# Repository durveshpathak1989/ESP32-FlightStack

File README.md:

# ESP32-FlightStack

ESP32-FlightStack is an open-source quadcopter flight-control stack for DIY drones, embedded-systems research, and low-cost UAV experimentation.

A custom quadcopter flight controller built around the **Adafruit HUZZAH32 / ESP32-WROOM-32E**, written in Arduino C++ on top of FreeRTOS. The project targets both stable flight and rigorous embedded-systems research: real-time scheduling, sensor fusion, Wi-Fi telemetry, onboard logging, runtime PID tuning, autonomous calibration, and over-the-air firmware updates, all on a $10 microcontroller.

**Firmware version:** v6.1.0<br>
**Control loop:** 400 Hz, `esp_timer`-driven, pinned to Core 1<br>
**AHRS default:** Attitude EKF (switchable at runtime to Mahony or Madgwick)

**Good GitHub topics:** `esp32`, `quadcopter`, `drone`, `uav`, `flight-controller`, `flight-control`, `embedded-c`, `esp-idf`, `arduino`, `freertos`, `pid-controller`, `imu`, `sensor-fusion`, `attitude-estimation`, `mpu9250`, `bmp280`, `madgwick-filter`, `motor-control`, `esc`

**Search keywords:** ESP32 drone library, ESP32 quadcopter flight controller, open-source drone stack, DIY quadcopter firmware, embedded drone control, IMU sensor fusion, PID stabilization, ESP32 UAV framework

---

## Open The Arduino Sketch

Open this file in Arduino IDE:

```text
RC_FlightController/RC_FlightController.ino
```

The folder name and the `.ino` file name match on purpose. Arduino expects that shape:

```text
RC_FlightController/
  RC_FlightController.ino
  src/
    Submodules/
      CalManager/
      IMU/
      Madgwick/
      MahonyAHRS/
      MotorControl/
      ...
```

Think of `RC_FlightController.ino` like the pilot, and `src/Submodules` like the toolbox beside the pilot. When Arduino builds the sketch, it automatically compiles the tools in `src/Submodules`, so you should not need to move the libraries by hand.

`Madgwick` and `MahonyAHRS` are also under `src/Submodules`, so Arduino compiles them automatically with the rest of the flight code. The shared AHRS types live in `src/Submodules/AHRS`.

After cloning with submodules, compile from the sketch folder:

```bash
git submodule update --init --recursive
arduino-cli compile --fqbn esp32:esp32:esp32 RC_FlightController
```

---

## Ground Station

| Dashboard | OTA upload | Offline OSM map |
|---|---|---|
|  |  |  |

---

## What This Project Does

Core loop:

```
Read IMU → notch-filter → AHRS/EKF → read RC → cascaded PID → motor mixer → ESC PWM
```

Surrounding infrastructure:

```
RC iBUS parsing           Autonomous sensor calibration
BMP280 barometer          GPS position + velocity
Wi-Fi AP + HTTP server    Browser-based ground station
Runtime PID / AHRS tuning Onboard high-speed CSV flight log
OTA firmware upload        Offline OSM map
Timing jitter measurement  Dynamic FFT notch tracking
CPU utilization monitor    ToF altitude sensor (optional)
```

Development philosophy:

```
1. Make the system safe.
2. Make the sensors trustworthy.
3. Make ACRO/rate mode stable.
4. Tune ANGLE/self-level mode.
5. Improve telemetry, logging, and test rigor.
```

---

## Capability Summary

| Area | Current capability |
|---|---|
| MCU | Adafruit HUZZAH32 Feather / ESP32-WROOM-32E |
| RTOS | Dual-core FreeRTOS, 7 tasks |
| IMU | MPU-9250 / MPU-6500 over SPI at 400 Hz |
| AHRS | Runtime-selectable: EKF (default), Mahony, Madgwick |
| Vibration filter | Static notch + dynamic FFT-tracked notch (45–170 Hz) |
| RC | FlySky FS-i6X + FS-iA6B iBUS, 200 Hz |
| Flight modes | ANGLE (self-level), ACRO (rate), DISARMED, FAILSAFE |
| Control | Cascaded angle+rate PID, yaw heading-hold |
| Motors | X-frame mixer, PWM ESCs via ESP32 LEDC |
| Barometer | BMP280 over I²C, 20 Hz, vertical speed estimate |
| GPS | u-blox NEO-6M / GY-GPS6MV2, NMEA UART, 50 Hz drain |
| Telemetry | ESP32 Wi-Fi AP + HTTP JSON endpoints |
| Ground station | Single-file HTML GCS, no build step |
| Runtime tuning | Full gain/filter payload via `/tune`, rejected while armed |
| Onboard logging | 100 Hz ring-buffer CSV log, 100 rows (1 s), streamed via HTTP |
| Timing log | Welford jitter stats + 800-sample ring buffer via `/timing` |
| OTA | Browser `.bin` upload via `/update`, safety-gated |
| Calibration | Autonomous gyro + 6-position accel + magnetometer + ESC via RC |
| Offline maps | Local `.osm` file loaded in browser, no internet required |
| CPU monitor | Per-core utilization estimate via idle hook |
| ToF | VL53L4CX optional altitude sensor (I²C shared with BMP280) |

---

## Hardware

| Subsystem | Part | Notes |
|---|---|---|
| Flight controller | Adafruit HUZZAH32 / ESP32-WROOM-32E | Main MCU, dual-core, Wi-Fi |
| IMU | MPU-9250 / MPU-6500 / GY-91 | Gyro + accel; onboard AK8963 mag if present |
| Barometer | BMP280 | Pressure, temperature, altitude |
| GPS | GY-GPS6MV2 / u-blox NEO-6M | Latitude, longitude, speed, satellites |
| RC transmitter | FlySky FS-i6X | 10-channel |
| RC receiver | FlySky FS-iA6B | iBUS serial protocol |
| ESCs | Standard PWM ESCs | 50 Hz PWM, 1000–2000 µs pulse |
| Motors | 2212-class, ~920 KV | Quadcopter propulsion |
| Battery | 3S LiPo (11.1 V nominal, 12.6 V full) | Main power, measured through GPIO34 divider |
| BEC | 5 V BEC | Powers controller and receiver |
| ToF (optional) | VL53L4CX | Altitude, shared I²C bus |

---

## Pin Map

| Function | GPIO | HUZZAH32 label | Direction | Notes |
|---|---:|---|---|---|
| SPI SCK | 5 | SCK | ESP32 → IMU | MPU-9250 clock |
| SPI MOSI | 18 | MO | ESP32 → IMU | MPU-9250 data in |
| SPI MISO | 19 | MI | IMU → ESP32 | MPU-9250 data out |
| MPU CS | 33 | 33 | ESP32 → IMU | Chip select |
| MPU INT | 27 | 27 | IMU → ESP32 | Wired but not driven by firmware |
| BMP280 SDA | 21 | SDA | Bidirectional | I²C data (shared with ToF) |
| BMP280 SCL | 22 | SCL | ESP32 → sensor | I²C clock (shared with ToF) |
| GPS RX | 13 | 13 | GPS TX → ESP32 | UART1 |
| GPS TX | 17 | 17 | ESP32 → GPS | UART1, optional |
| iBUS RX | 16 | 16 | Receiver → ESP32 | UART2 |
| iBUS TX | 4 | 4 | — | Spare, not connected |
| Motor FL | 25 | 25 | ESP32 → ESC | Front-left, CCW |
| Motor FR | 15 | 15 | ESP32 → ESC | Front-right, CW |
| Motor RL | 14 | 14 | ESP32 → ESC | Rear-left, CW |
| Motor RR | 32 | 32 | ESP32 → ESC | Rear-right, CCW |
| Battery ADC | 34 | 34 | Divider -> ESP32 | ADC1 input-only; 235k/35k divider, sampled every 500 ms |

Free GPIO: 23 (cleanest), 26 (ADC2/Wi-Fi caveat), 36/39 (input-only). GPIO34 is used by the battery ADC.

### Battery Voltage Monitor

GPIO34 reads the 3S pack through a high-value divider and updates telemetry every 500 ms. The firmware is configured for:

```
Battery + -> 235k -> ADC node -> 35k -> GND
ADC node -> GPIO34
Divider scale: 7.7143
```

A 12.2 V pack should measure about 1.58 V at GPIO34. Use a multimeter on the ADC node before plugging into the ESP32; the ADC pin must stay below 3.3 V. A 1k series resistor into GPIO34 and a 0.1 uF capacitor from GPIO34 to GND are recommended for noise filtering and input protection. If your real resistor values differ, update `BATTERY_RTOP_OHMS`, `BATTERY_RBOTTOM_OHMS`, or `BATTERY_ADC_CAL_SCALE` in `RC_FlightController.ino`.

---

## Wiring Guide

### MPU-9250 / GY-91

| IMU pin | ESP32 pin | Notes |
|---|---|---|
| VCC | 3.3 V | Use 3.3 V only |
| GND | GND | Common ground |
| SCL / SCLK | GPIO 5 | SPI clock |
| SDA / MOSI | GPIO 18 | SPI MOSI |
| AD0 / MISO | GPIO 19 | SPI MISO |
| NCS / CS | GPIO 33 | Chip select — pull-up to 3.3 V if unused |
| INT | GPIO 27 | Wired to GPIO 27; firmware does not use it |

Expected `WHO_AM_I`:

```
0x71  MPU-9250
0x70  MPU-6500 / MPU-9250 gyro-accel die
```

If the AK8963 magnetometer is absent or unresponsive, roll and pitch remain accurate. Yaw will drift without magnetic heading correction.

---

### BMP280

| BMP280 pin | ESP32 pin | Notes |
|---|---|---|
| VCC | 3.3 V | |
| GND | GND | |
| SDA / SDI | GPIO 21 | I²C data |
| SCL / SCK | GPIO 22 | I²C clock |
| CSB | 3.3 V | Pull high to force I²C mode |
| SDO | GND or 3.3 V | GND → address `0x76`, 3.3 V → `0x77` |

The firmware scans both addresses automatically. If nothing is found, verify CSB is pulled high and SDO is tied to a rail.

---

### GPS (GY-GPS6MV2 / NEO-6M)

| GPS pin | ESP32 pin | Notes |
|---|---|---|
| VCC | 3.3 V or module VIN | Many NEO-6M boards have an onboard regulator |
| GND | GND | |
| TXD | GPIO 13 | GPS → ESP32 (UART1 RX) |
| RXD | GPIO 17 | ESP32 → GPS (optional) |

```
UART:     UART1
Baud:     9600
Protocol: NMEA 0183
Parsed:   GPRMC, GPGGA
```

Cold fix outdoors: 30–90 seconds. Indoor fix is unreliable. A blinking blue LED on the module typically indicates a live fix.

---

### FlySky FS-iA6B iBUS

| Receiver pin | ESP32 pin | Notes |
|---|---|---|
| iBUS port | GPIO 16 | UART2 RX — use the dedicated iBUS/S.BUS port |
| VCC | 5 V from BEC | Receiver accepts 4.0–6.5 V |
| GND | GND | |

```
UART:         UART2
Baud:         115200
Frame length: 32 bytes
Frame period: ~7 ms
Rate:         ~142 Hz from receiver, polled at 200 Hz by firmware
```

Use the **iBUS port** on the receiver, not the individual CH1–CH6 servo outputs.

---

### ESC and Motor

| Motor | GPIO | Position | Spin | Notes |
|---|---:|---|---|---|
| FL | 25 | Front-left | CCW | 33 Ω series resistor recommended |
| FR | 15 | Front-right | CW | 33 Ω series resistor recommended |
| RL | 14 | Rear-left | CW | 33 Ω series resistor recommended |
| RR | 32 | Rear-right | CCW | 33 Ω series resistor recommended |

ESC ground and ESP32 ground must share a common reference. Without this, motor signals behave unpredictably.

---

## Motor Layout and Mixer

X-frame, viewed from above:

```
            Front

    FL  CCW          FR  CW
    GPIO 25          GPIO 15

         \           /
          \         /
           \       /
            ---X---
           /       \
          /         \
         /           \

    RL  CW           RR  CCW
    GPIO 14          GPIO 32

            Rear
```

Mixer equations:

```
FL = throttle + rollOut - pitchOut - yawOut
FR = throttle - rollOut - pitchOut + yawOut
RL = throttle + rollOut + pitchOut + yawOut
RR = throttle - rollOut + pitchOut - yawOut
```

Before first flight, verify signs by hand with props removed:

- Tilt right → correction must push right side up.
- Tilt left → correction must push left side up.
- Tilt nose down → correction must push nose up.
- Tilt nose up → correction must push nose down.
- Any reversal means a motor order, IMU axis sign, or mixer sign error. Fix it in code, not with PID tuning.

---

## RC Channel Mapping

| Channel | Transmitter control | Firmware function |
|---|---|---|
| CH1 | Right stick L/R | Roll |
| CH2 | Right stick U/D | Pitch |
| CH3 | Left stick U/D | Throttle |
| CH4 | Left stick L/R | Yaw |
| CH5 | VrA knob | Spare |
| CH6 | VrB knob | ESC calibration trigger (full-right = request) |
| CH7 | SWA | Arm / disarm |
| CH8 | SWB | ANGLE / ACRO mode |
| CH9 | SWC | Accelerometer calibration confirmation |
| CH10 | SWD | Calibration trigger (rising edge, disarmed only) |

---

## Flight Modes

### DISARMED

Motors are off. Permitted actions:

- Sensor calibration
- Runtime tuning via `/tune`
- OTA upload via `/update`
- Bench sensor checks
- Level-zero capture (SWB high while disarmed)

### ANGLE mode

Self-leveling. The stick commands a target lean angle. When the stick centres, the target returns to zero and the quad levels itself.

```
RC stick → target angle → angle PID → target rate → rate PID → motor mixer
```

Tune ACRO mode first. Then add ANGLE mode.

### ACRO mode

Rate mode. The stick commands angular velocity. Releasing the stick stops rotation but does not self-level.

```
RC stick → target rate → rate PID → motor mixer
```

### Yaw heading hold

When the yaw stick is within `yaw_deadband` of centre, the firmware holds the last commanded heading using a yaw angle PID. Moving the stick beyond the deadband switches to rate mode for yaw.

### FAILSAFE

If iBUS frames stop arriving, the receiver driver marks the signal invalid and motor outputs are cut immediately.

---

## FreeRTOS Task Architecture

| Task | Core | Priority | Stack (words) | Rate | Purpose |
|---|---:|---:|---:|---:|---|
| `taskControl` | 1 | 5 | 10240 | 400 Hz (esp_timer) | IMU, AHRS, PID, motor output |
| `taskRC` | 0 | 3 | 6144 | 200 Hz | iBUS parsing, arm/cal triggers |
| `taskGPS` | 0 | 1 | 4096 | 50 Hz | GPS NMEA drain and parse |
| `taskSerial` | 0 | 1 | 4096 | 20 Hz | Serial status and PID trace |
| `taskBMP` | 0 | 1 | 3072 | 20 Hz | BMP280 read, vertical speed |
| `taskCPU` | 0 | 1 | 3072 | 2 Hz | CPU utilization estimate |
| `taskWiFi` | 0 | 1 | 12288 | Event-driven | HTTP server, telemetry, OTA |

Core 1 is entirely dedicated to the control loop. All communication and slower sensors run on Core 0.

The control loop is released by an `esp_timer` ISR calling `xTaskNotifyGive()` every 2500 µs. `vTaskDelay()` is not used in `taskControl` because the FreeRTOS tick resolution on this build can be coarser than 2.5 ms.

---

## AHRS / Attitude Estimation

The firmware supports three attitude estimators, switchable at runtime via `/tune` without rebooting:

| Mode | `ahrs_filter_mode` | Description |
|---|---:|---|
| EKF (default) | 0 | 6-DOF or 9-DOF extended Kalman filter with gyro bias estimation |
| Mahony | 1 | Complementary filter, fast, low CPU cost |
| Madgwick | 2 | Gradient-descent complementary filter |

Switching estimator resets both EKF and Madgwick state to avoid attitude transients from stale quaternions.

**Pipeline order:** raw IMU → static notch filter → dynamic notch filter → AHRS → PID.

---

## Signal Filtering

### Static notch filter

A biquad notch filter is applied to all 6 IMU axes (3 accel + 3 gyro) before the AHRS. Default centre frequency: 90 Hz, Q: 8. Both are tunable at runtime.

### Dynamic FFT notch tracking

The `SpectrumAnalyzer` collects IMU data and runs an FFT. Every 250 ms (10 Hz), `updateDynamicNotchFromFFT()` finds the dominant gyro peak in the 45–170 Hz range and updates the notch centre frequency toward it using an exponential smoothing step capped at 2 Hz per update. The notch will not track while disarmed or below 15% throttle.

---

## Runtime Tuning

POST to `/tune` with a JSON body while **disarmed**. Any key can be omitted. The request is rejected while armed.

### Pilot limits

| Key | Default | Meaning |
|---|---:|---|
| `max_angle_deg` | 5.0 | Maximum lean in ANGLE mode (degrees) |
| `max_rate_dps` | 120.0 | Maximum roll rate in ACRO (deg/s) |
| `max_pitch_rate_dps` | 120.0 | Maximum pitch rate in ACRO (deg/s) |
| `yaw_max_rate_dps` | 20.0 | Maximum yaw rate (deg/s) |
| `yaw_deadband` | 0.02 | Stick fraction below which heading hold activates |

### PID authority limits

| Key | Default | Meaning |
|---|---:|---|
| `roll_output_limit` | 0.120 | Max roll correction before mixing |
| `pitch_output_limit` | 0.120 | Max pitch correction before mixing |
| `yaw_output_limit` | 0.120 | Max yaw correction before mixing |

### Throttle shaping

| Key | Default | Meaning |
|---|---:|---|
| `throttle_expo` | 0.70 | Softens low-throttle response |
| `throttle_up_rate_per_sec` | 0.50 | Max throttle increase rate per second |
| `throttle_down_rate_per_sec` | 0.50 | Max throttle decrease rate per second |
| `motor_idle` | 0.08 | Minimum motor output when armed and throttle above cut |
| `motor_max` | 1.00 | Maximum motor output cap |
| `throttle_cut` | 0.03 | Below this throttle, motors are cut |
| `idle_ramp_end` | 0.15 | Throttle fraction where idle blending ends |

### Rate PID (inner loop)

| Key | Default |
|---|---:|
| `pid_roll_kp` | 0.000900 |
| `pid_roll_ki` | 0.000001 |
| `pid_roll_kd` | 0.000000010 |
| `pid_pitch_kp` | 0.001900 |
| `pid_pitch_ki` | 0.000001 |
| `pid_pitch_kd` | 0.000000010 |
| `pid_yaw_kp` | 0.008000 |
| `pid_yaw_ki` | 0.00100 |
| `pid_yaw_kd` | 0.00000 |
| `pid_ilimit` | 50.0 |

### Angle PID (outer loop)

| Key | Default |
|---|---:|
| `pid_angle_roll_kp` | 1.50 |
| `pid_angle_roll_ki` | 0.00 |
| `pid_angle_roll_kd` | 0.000 |
| `pid_angle_pitch_kp` | 1.00 |
| `pid_angle_pitch_ki` | 0.00 |
| `pid_angle_pitch_kd` | 0.000 |
| `pid_angle_yaw_kp` | 1.00 |

### Notch filter

| Key | Default | Meaning |
|---|---:|---|
| `notch_enable` | true | Enable static notch |
| `notch_freq_hz` | 143.84 | Centre frequency (Hz) |
| `notch_q` | 10.0 | Q factor — higher = narrower |

### AHRS

| Key | Default | Meaning |
|---|---:|---|
| `ahrs_filter_mode` | 0.0 | 0 = EKF, 1 = Mahony, 2 = Madgwick |
| `mahony_kp` | (from object) | Mahony proportional gain |
| `mahony_ki` | (from object) | Mahony integral gain |
| `madgwick_beta` | 0.080 | Madgwick beta |

### Attitude EKF

| Key | Default | Meaning |
|---|---:|---|
| `ekf_angle_q` | 0.0008 | Process noise — angle states |
| `ekf_bias_q` | 0.000001 | Process noise — gyro bias states |
| `ekf_accel_r` | 0.400 | Accel measurement noise (higher = trust less) |
| `ekf_mag_r` | 0.200 | Magnetometer measurement noise |
| `ekf_mag_declination_deg` | 0.0 | Local magnetic declination |
| `ekf_mag_yaw_offset_deg` | 0.0 | Yaw alignment offset |
| `ekf_mag_yaw_sign` | 1.0 | +1 or -1 to correct mag axis sign |

---

## Serial Commands

| Command | Effect |
|---|---|
| `p` | Toggle ~4 Hz `[PID]` tuning trace on/off (off at boot) |

---

## HTTP Endpoints

The ESP32 creates a Wi-Fi access point:

```
SSID:     ESP32-DRONE
Password: 12345678
IP:       192.168.4.1
```

| Endpoint | Method | Purpose |
|---|---|---|
| `/telemetry` | GET | Full flight state JSON |
| `/tune` | POST | Apply PID / AHRS / filter gains (disarmed only) |
| `/log?since=N` | GET | Calibration and system log lines since index N |
| `/timing` | GET | Jitter stats JSON (Welford mean, std, max, violations) |
| `/timing/reset` | POST | Reset jitter accumulator |
| `/timing/csv` | GET | Raw 800-sample period ring buffer as CSV |
| `/flightlog/csv` | GET | Freeze and download 100-row onboard flight log CSV |
| `/flightlog/reset` | POST | Clear onboard log and resume writing |
| `/update` | GET | OTA upload page |
| `/update` | POST | OTA firmware upload (disarmed, throttle low, motors off) |

Battery telemetry fields from `/telemetry`: `batteryVoltageV`, `batteryAdcV`, `batteryCellV`, `batteryPercent`, `batteryValid`, `batteryLow`, and `batteryCritical`.

---

## Onboard Flight Log

The firmware maintains a 100-row ring buffer sampled at 100 Hz (every 4th control cycle). Each row is approximately 320 bytes and captures:

```
Timestamps and loop count       RC stick inputs (all 10 channels)
IMU timing phases               Throttle (raw, shaped, smoothed)
Period and jitter               AHRS attitude (roll, pitch, yaw)
Raw and filtered IMU data       Control attitude (after level-zero offset)
Magnetometer                    PID targets, errors, and outputs
EKF gyro bias estimates         Motor commands and estimated RPM
Notch filter state              BMP280 altitude and vertical speed
AHRS mode and mag-accept flag   CPU utilization (Core 0 and Core 1)
```

Workflow:

```
POST /flightlog/reset  → clears buffer and re-enables writing
ARM + fly
DISARM
GET  /flightlog/csv    → freezes buffer and streams CSV
```

To extend the log beyond 1 second, increase `FLIGHT_LOG_SIZE` (currently 100). At 320 bytes per row and ~300 KB free heap in a typical flight build, 300 rows (~3 seconds) is a safe upper bound.

---

## Autonomous Calibration

Calibration runs inside `taskControl` on Core 1 and is triggered by RC or HTTP. While calibration is active, the flight loop is blocked and motor outputs are inhibited.

### IMU calibration (guided, via SWD + SWC)

1. **Disarm** the craft (SWA low).
2. Flip **SWD** up to request calibration.
3. **Gyro phase** (automatic): place the drone flat and still. The firmware waits 3 seconds for settling, then samples 5 seconds of gyro data.
4. **Accel phase** (6 positions): flip **SWC** up to confirm each orientation. The firmware prompts each pose over the serial log.
5. **Magnetometer phase** (if present): rotate the drone slowly in all axes for 30 seconds.
6. Calibration saves to NVS (non-volatile storage) and loads automatically on every subsequent boot.

### ESC calibration (via VrB + SWC)

1. **Disarm** and set throttle to minimum.
2. Raise **VrB** (CH6) to full right.
3. Confirm with **SWC** when prompted.
4. Lower VrB to cancel at any time.

Calibration is rejected if the craft is armed or throttle is above `throttle_cut`.

---

## Software Level-Zero Trim

While **disarmed** with **SWB** held high (ACRO position), the firmware averages 1.2 seconds of AHRS attitude output and saves it as a roll/pitch/yaw offset. All subsequent control attitude values are computed relative to this zero. This corrects for frame twist or a non-level mounting surface without touching IMU calibration or the AHRS quaternion.

---

## Wi-Fi Ground Station

The browser-based GCS (`Simulation/DroneGCS.html`) connects directly to `http://192.168.4.1`. No build step or internet connection is required once the file is open.

Features:

- Live attitude display (roll, pitch, yaw)
- Motor output gauges
- Battery voltage, percentage, and low/critical visual
- PID output traces
- Barometer altitude and vertical speed
- GPS position and satellite count
- Timing jitter chart
- Full PID, AHRS, and filter tuning panel
- Calibration log stream
- OTA firmware upload panel

---

## Offline OSM Map

When connected to `ESP32-DRONE`, the laptop has no internet. Tile-based maps will not load. The offline OSM workflow serves a local map extract from the laptop instead.

Recommended folder layout:

```
DroneGCS/
├── DroneGCS.html
└── YourArea.osm
```

Run a local server:

```bash
cd path/to/DroneGCS
python3 -m http.server 8080
```

Open in the browser:

```
http://localhost:8080/DroneGCS.html
```

The GCS fetches telemetry from `http://192.168.4.1` while the OSM file is loaded locally. Use only a small OSM extract around your test field — large files slow the browser significantly.

Good sources for OSM extracts:

- OpenStreetMap.org export (small bounding box)
- BBBike extract service
- Geofabrik extract, cropped with Osmium or QGIS

The map is for situational awareness only — it is not autonomous navigation.

---

## OTA Firmware Update

### Arduino IDE partition scheme

Select before the first USB flash:

```
Tools → Partition Scheme → Minimal SPIFFS (1.9MB APP with OTA and 190KB SPIFFS)
```

This provides two app slots for OTA while giving the application maximum flash space. The GCS is served from the laptop, so a large SPIFFS partition is not needed.

Do **not** use `No OTA` or `Huge APP without OTA`.

### Exporting the binary

1. Select the correct board and partition scheme.
2. Flash once by USB.
3. Click **Sketch → Export Compiled Binary**.
4. Click **Sketch → Show Sketch Folder** and find the build output.
5. Upload the correct file through OTA:

```
RC_FlightController.ino.bin          ← upload this
```

Do not upload:

```
boot_app0.bin
RC_FlightController.ino.bootloader.bin
RC_FlightController.ino.partitions.bin
RC_FlightController.ino.merged.bin
RC_FlightController.ino.elf
```

### OTA safety gate

The firmware permits OTA only when all three conditions hold:

```
armed == false
throttle <= throttle_cut
all motor outputs <= 0.001
```

Remove propellers before every OTA session.

---

## First-Time Setup

### Step 1 — Bench safety

```
REMOVE PROPELLERS
```

### Step 2 — Flash firmware

```
Board:          Adafruit ESP32 Feather
Upload speed:   921600
Partition:      Minimal SPIFFS (1.9MB APP with OTA)
```

### Step 3 — Read the boot log

Open Serial Monitor at **115200 baud**. Expected output:

```
[BOOT] IMU... OK
[BOOT] AK8963 magnetometer: DETECTED  (or NOT FOUND)
[BOOT] BMP280... OK  (or not found)
[BOOT] GPS (GY-GPS6MV2)...
[BOOT] NVS calibration... loaded  (or none)
[BOOT] iBUS ready.
[BOOT] All tasks running.
[BOOT] Ground station: http://192.168.4.1
[BOOT] Free heap: XXXXXX bytes
```

If the IMU fails, halt is immediate — check SPI wiring and 3.3 V power.

### Step 4 — Check RC

Turn on the transmitter and confirm:

```
[iBUS] ~142 Hz good | 0 bad/s | 0 bad total   (should appear every second)
```

Confirm sticks, SWA arm/disarm, SWB mode change, SWD calibration trigger.

### Step 5 — Calibrate sensors

With props removed:

1. Keep SWA disarmed.
2. Flip SWD up (rising edge triggers calibration).
3. Follow prompts in the serial log.
4. Calibration saves to NVS and reloads on every boot.

### Step 6 — Verify motor order and mixer

With props still removed:

- Arm the craft.
- Raise throttle slightly.
- Confirm FL/FR/RL/RR match physical position.
- Tilt the frame by hand and confirm PID corrections oppose the tilt.
- Disarm before anything else.

### Step 7 — First powered hover

```
Small props
max_angle_deg = 10
motor_max = 0.60
angle I gains = 0
Conservative throttle
Short hover bursts
```

Do not attempt to hover until Step 6 is confirmed.

---

## Tuning Order

1. Props off: verify sensor sign and motor correction direction (Step 6).
2. ACRO mode first: tune `pid_roll_kp`, `pid_pitch_kp` for stable rate response with no oscillation.
3. Add `kd` carefully — unfiltered derivative amplifies gyro noise at 400 Hz.
4. ANGLE mode second: tune `pid_angle_roll_kp`, `pid_angle_pitch_kp`.
5. Keep angle I gains at zero until P and D are settled.
6. Tune yaw separately — yaw authority is intentionally limited to `yaw_output_limit = 0.2`.
7. Use `/flightlog/csv` and the timing monitor to verify loop timing stays within budget during tuning.

---

## Timing Diagnostics

`GET /timing` returns a JSON object with:

```json
{
  "count": 12000,
  "target_us": 2500,
  "period_mean_us": 2501.3,
  "period_std_us": 18.4,
  "jitter_max_us": 142,
  "jitter_mean_us": 12.1,
  "jitter_violations": 3,
  "violation_thresh_us": 100,
  "p50_us": 2500,
  "p95_us": 2528,
  "p99_us": 2571
}
```

`GET /timing/csv` streams the last 800 raw period samples for offline analysis.

`POST /timing/reset` clears all accumulators for a clean measurement window.

The `[TIME]` serial line prints once per second:

```
[TIME] period=2501us jitter=+1us ctrl=XXXus full=XXXus headroom=+XXXus ...
```

A negative `headroom` value means a control overrun — the current cycle took longer than the 2500 µs budget.

---

## Troubleshooting

### Serial garbage

Baud rate must be **115200**. Confirm in the IDE Serial Monitor and any terminal emulator.

### IMU not found

```
3.3 V power to MPU
SPI wiring: SCK=5, MOSI=18, MISO=19, CS=33
No other SPI device sharing the bus without its own CS
```

### BMP280 not found

```
SDA=21, SCL=22
CSB pulled high to 3.3 V
SDO set for expected I²C address (0x76 or 0x77)
3.3 V power
```

### GPS no fix

```
Move outdoors with clear sky
Wait 30–90 seconds for cold fix
GPS TXD → GPIO 13
Antenna facing up
```

### No RC input / failsafe

```
iBUS port on receiver, not servo pins
GPIO 16 connected to iBUS signal wire
Receiver powered from 5 V BEC
Transmitter bound and powered
```

### Drone tips on throttle

Diagnose in this order:

1. Motor order (FL/FR/RL/RR positions).
2. Prop direction (CW/CCW per motor position).
3. ESC signal wiring.
4. IMU axis signs.
5. Mixer signs.
6. Centre of gravity.
7. Frame twist.
8. PID gains (only after all above are confirmed correct).

**Never use PID tuning to compensate for a motor order or sign error.**

### GPS map blank

When connected to `ESP32-DRONE`, the laptop has no internet. Use the offline OSM workflow, or connect both devices to a shared hotspot.

### OTA rejected

OTA is gated on disarmed + throttle low + motors off. Confirm all three in the GCS or serial log before uploading.

---

## Known Firmware Issues (v6.1.0)

The following issues are identified and tracked for the next release:

| # | Issue | Impact |
|---|---|---|
| 1 | `[MOTOR_SAT]` Serial.printf fires unconditionally at 400 Hz | Guaranteed control overrun while armed |
| 2 | Motor writes throttled to 200 Hz (`MOTOR_UPDATE_PERIOD_US = 5000`) | Up to 5 ms stale motor command per cycle |
| 3 | `[DYN_NOTCH_HOOK]` and `[DYN_FFT_INPUT]` debug prints inside the 400 Hz IMU block | ~7 ms Serial cost on the cycle they fire |
| 4 | `thrSmooth` static local not reset on disarm | Inherited throttle state after disarm/re-arm |
| 5 | AHRS mode falls back to EKF (mode 0) on mutex miss | One-cycle estimator switch during flight |
| 6 | `calLog()` called from Core 1 inside `applyTuningToObjects()` | Priority inversion risk against Wi-Fi task |
| 7 | Unfiltered derivative term in PID | Gyro noise amplification at high Kd |
| 8 | Single `pid_ilimit = 50` shared across rate (dps) and angle (deg) loops | Dimensionally inconsistent wind-up limit |
| 9 | `FLIGHT_LOG_SIZE = 100` but comment says 300 | Log is 1 s, not 3 s |
| 10 | GPIO34 battery divider calibration needs a real-hardware multimeter check | Incorrect divider ratio skews percentage and RPM estimate |

---

## Safety Rules

- **Remove propellers** before USB flashing, OTA, calibration, or bench tests.
- Never arm on USB power alone.
- Never attempt OTA while armed.
- Never tune while armed (the firmware enforces this for `/tune`).
- Keep first hover tests short and low.
- Use smaller props during early PID tuning.
- Keep a USB recovery path available at all times.
- GPS and map display are telemetry only — not navigation authority.

---

## Project Direction

This project supports both flight testing and embedded-systems research:

- ESP32 dual-core task partitioning and priority assignment
- `esp_timer` vs `vTaskDelay` for hard real-time control loops
- Wi-Fi interference with control-loop timing (characterised via `/timing`)
- Runtime filter tuning and AHRS mode switching without reboot
- OTA update safety gating
- Autonomous calibration usability over RC
- Offline field-map workflow
- Low-cost AHRS comparison (EKF vs Mahony vs Madgwick)
- Onboard high-speed logging for post-flight analysis
- LSTM-based fault prognosis using logged CSV data (companion research project)

The goal is a flying quadcopter that is also a rigorous test platform for every subsystem interaction.

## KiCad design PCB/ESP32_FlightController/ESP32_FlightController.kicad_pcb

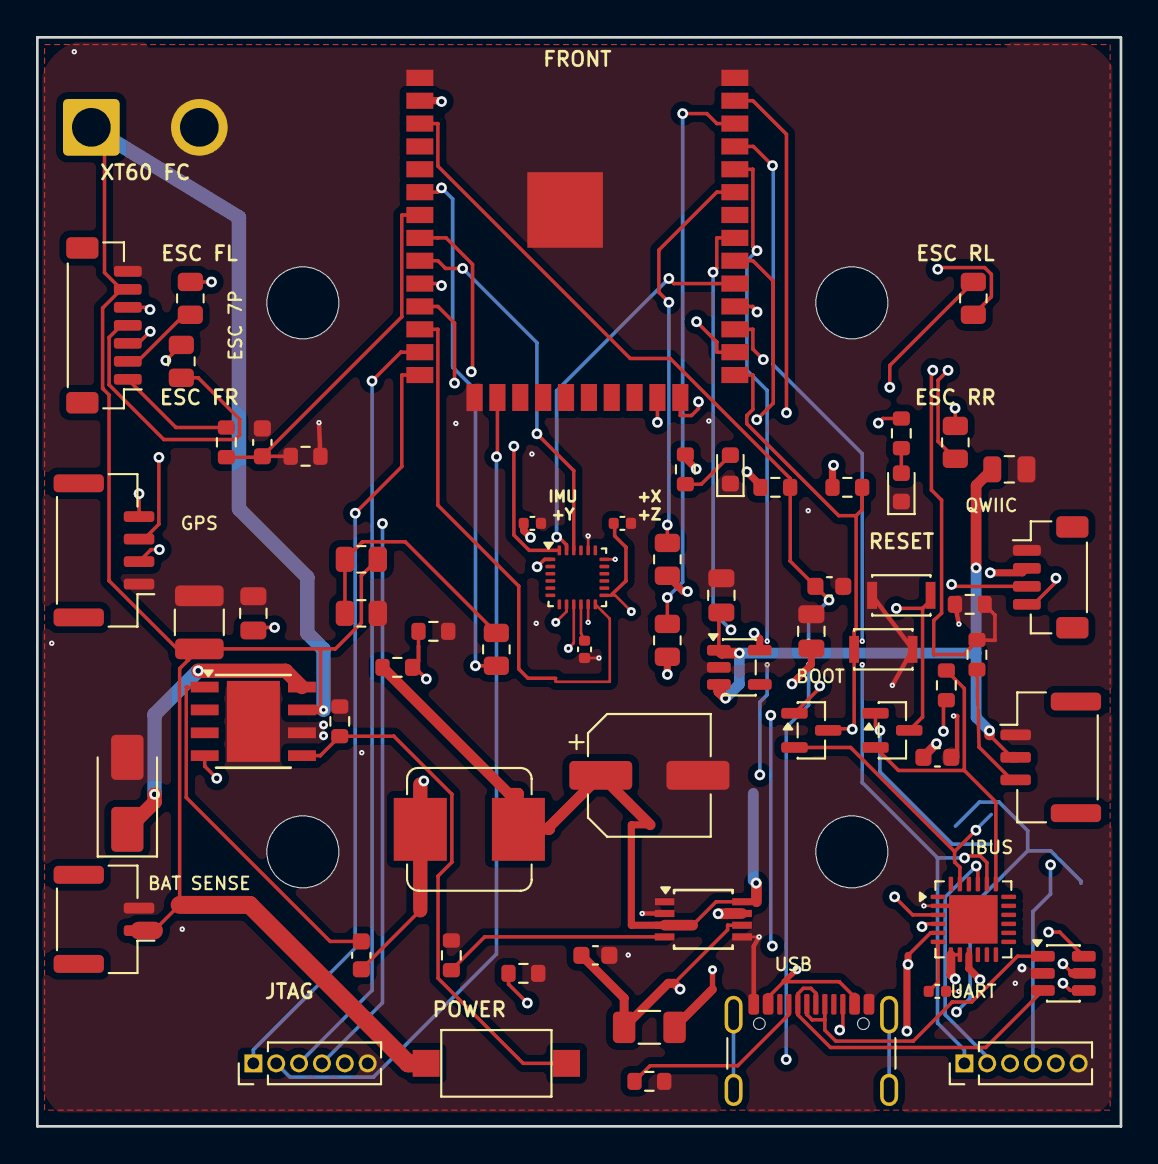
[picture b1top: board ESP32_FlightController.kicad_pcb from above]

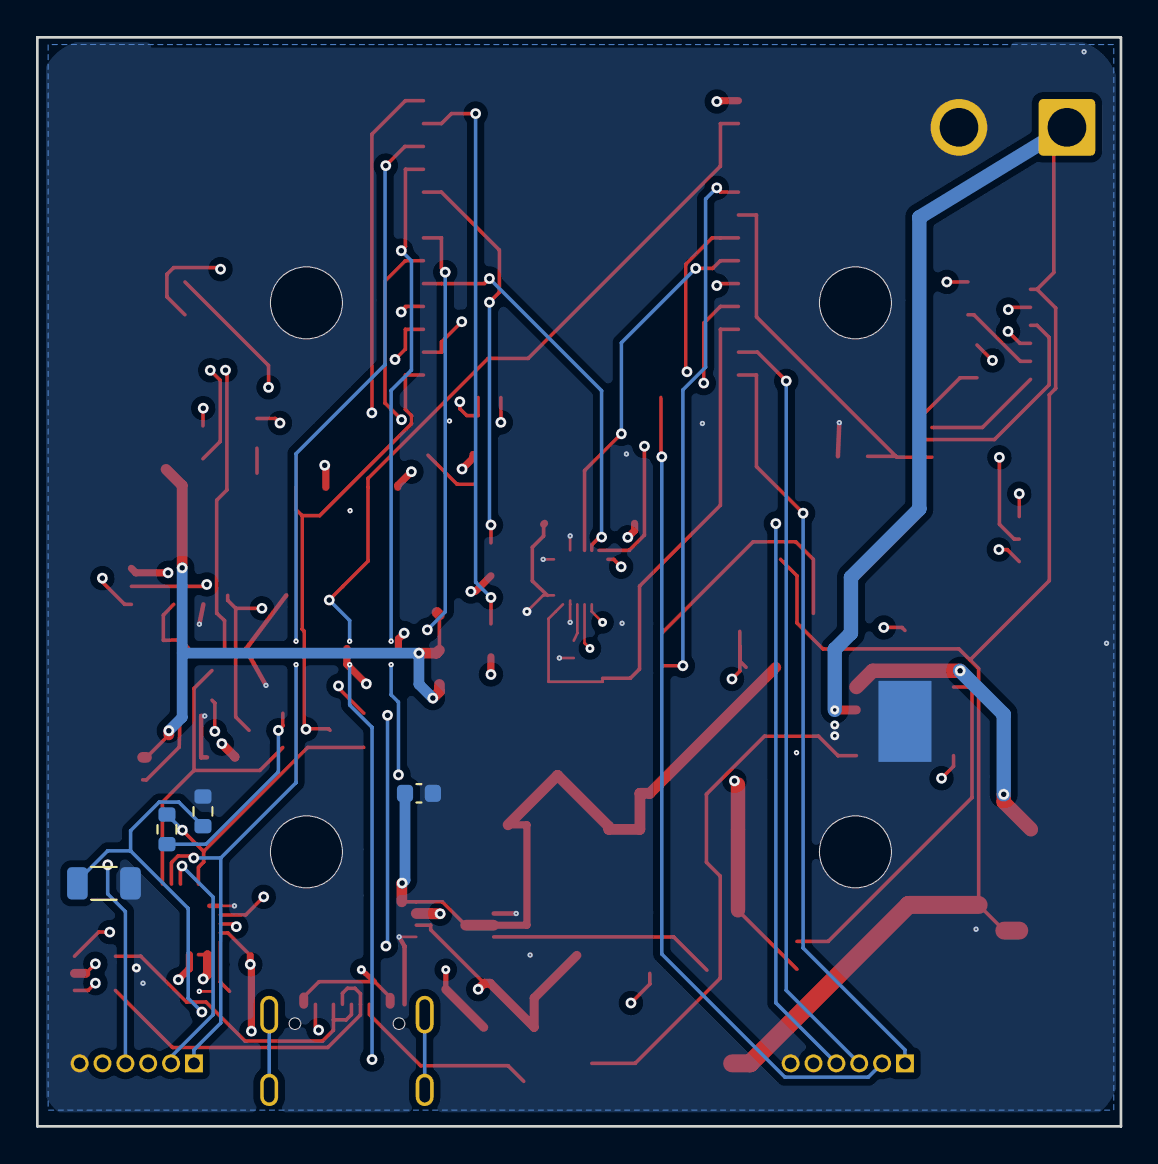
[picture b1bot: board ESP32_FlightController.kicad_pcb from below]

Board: 4 copper layers, 60.2 x 60.5 mm, 73 parts (4 on the bottom side), 59 nets.

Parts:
C1: 10uF/25V X7R; C_1210_3225Metric
C2: 100n; C_0805_2012Metric
C3: 10n; C_0603_1608Metric
C4: 220uF/10V LOW-ESR; CP_Elec_6.3x5.8
C5, C6: 10u; C_0805_2012Metric
C7: 1u; C_0603_1608Metric
C10: 10n X7R; C_0402_1005Metric
C11, C12, C13: 100n X7R; C_0402_1005Metric
C14: 4.7u X7R; C_0603_1608Metric
C15, C16, C19: 100n; C_0603_1608Metric
C17: 10u X7R; C_0805_2012Metric
C18: 1nF/2kV; C_1206_3216Metric
D1: B340A; D_SMA
D3: GREEN_POWER; LED_0603_1608Metric
D4: BLUE_STATUS; LED_0603_1608Metric
F1: 0.75A USB PTC; Fuse_1206_3216Metric
H1, H2, H3, H4: M4 / 30.5mm STACK; MountingHole_4mm
J1: XT60_FC_FEED_PIGTAIL; SolderWire-1.5sqmm_1x02_P6mm_D1.7mm_OD3mm
J2: 3S_BAT_SENSE; JST_GH_BM02B-GHS-TBT_1x02-1MP_P1.25mm_Vertical
J4: I2C_SENSOR_BUS; JST_SH_BM04B-SRSS-TB_1x04-1MP_P1.00mm_Vertical
J5: GPS_NEO6M; JST_GH_BM04B-GHS-TBT_1x04-1MP_P1.25mm_Vertical
J6: FLYSKY_IBUS; JST_GH_BM03B-GHS-TBT_1x03-1MP_P1.25mm_Vertical
J7: UART_PROGRAM; PinHeader_1x06_P1.27mm_Vertical
J8: JTAG_DEBUG; PinHeader_1x06_P1.27mm_Vertical
J9: USB_C_PROGRAM; USB_C_Receptacle_GCT_USB4105-xx-A_16P_TopMnt_Horizontal
J14: BLS60A_ESC_7PIN; JST_SH_BM07B-SRSS-TB_1x07-1MP_P1.00mm_Vertical
L1: 15uH SRP7028A-150M; L_Bourns_SRP7028A_7.3x6.6mm
Q1, Q2: MMBT3904; SOT-23
R1: 235k 1%; R_0805_2012Metric
R2: 35k 1%; R_0805_2012Metric
R3: 1k; R_0805_2012Metric
R4, R5: 4.7k; R_0805_2012Metric
R6, R21, R25: 10k 1%; R_0603_1608Metric
R7: 3.24k 1%; R_0603_1608Metric
R8, R9, R18, R19: 10k; R_0603_1608Metric
R10, R11, R12, R13: 220; R_0805_2012Metric
R14: 100k; R_0603_1608Metric
R15, R16: 5.1k; R_0603_1608Metric
R17: 499R (1A LIMIT); R_0603_1608Metric
R20: 1M; R_0603_1608Metric
R22, R23: 2.2k; R_0603_1608Metric
R24, R26: 20k 1%; R_0603_1608Metric
SW1: RESET; SW_SPST_CK_KXT3
SW2: CONTROLLER_POWER; SW_SPST_CK_RS282G05A3
SW3: BOOT; SW_SPST_CK_KXT3
U1: ESP32-WROOM-32E; ESP32-WROOM-32_Custom
U2: MPU-9250; InvenSense_QFN-24_3x3mm_P0.4mm
U3: TPS5430DDA; TI_SO-PowerPAD-8_NoUnderDrills
U4: AP2112K-3.3; SOT-23-5
U5: USBLC6-2SC6; SOT-23-6
U6: CP2102N-A02-GQFN24; QFN-24-1EP_4x4mm_P0.5mm_EP2.7x2.7mm
U7: TPS2113APW; TSSOP-8_3x3mm_P0.65mm

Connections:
+3V3: C6.1, C10.1, C11.1, J4.2, J5.2, J7.5, J8.5, R4.1, R5.1, R8.1, R9.1, R22.2, U1.2 (VDD), U2.1 (RESV_VDDIO), U2.8 (VDDIO), U2.13 (VDD), U4.5 (VOUT), U6.5 (VIO), U6.9 (~RST)
+5V: C5.1, C17.1, J6.2, U4.1 (VIN), U4.3 (EN), U7.7 (OUT)
/+5V_BUCK: C4.1, C15.1, L1.2, R6.1, U7.3 (VSNS), U7.8 (IN1)
/AUTO_DTR: Q2.2 (E), R18.2, U6.23 (~DTR)
/AUTO_RTS: Q1.2 (E), R19.2, U6.19 (~RTS)
/BAT_ADC: C2.1, R3.1, U1.6 (IO34)
/BOOT_IO0: J7.4, Q2.3 (C), R9.2, SW3.1, U1.25 (IO0)
/BOOT_STATUS_LED: R23.2, U1.24 (IO2)
/BUCK_EN: R14.1, SW2.2 (B), U3.5 (EN)
/CP2102_VDD: C13.1, U6.6 (VDD)
/ESC_CURRENT_ADC: C19.1, R21.1, R24.1, U1.7 (IO35)
/ESC_CUR_RAW: J14.1, R21.2
/ESP_EN: C7.1, J7.3, Q1.3 (C), R8.2, SW1.2, U1.3 (EN)
/GPS_RX: J5.4, U1.37 (IO23)
/GPS_TX: J5.3, U1.28 (IO17)
/I2C_SCL: J4.3, R5.2, U1.36 (IO22)
/I2C_SDA: J4.4, R4.2, U1.33 (IO21)
/IBUS_RAW: J6.3, R25.2
/IBUS_RX: R25.1, R26.1, U1.27 (IO16)
/IMU_CS: U1.9 (IO33), U2.22 (~CS)
/IMU_INT: U1.12 (IO27), U2.12 (INT)
/JTAG_TCK: J8.2, U1.16 (IO13)
/JTAG_TDI: J8.1, U1.14 (IO12)
/JTAG_TDO: J8.4, U1.23 (IO15)
/JTAG_TMS: J8.3, U1.13 (IO14)
/MOTOR_FL: J14.2, R10.1
/MOTOR_FL_RAW: R10.2, U1.10 (IO25)
/MOTOR_FR: J14.4, R11.1
/MOTOR_FR_RAW: R11.2, U1.26 (IO4)
/MOTOR_RL: J14.3, R12.1
/MOTOR_RL_RAW: R12.2, U1.11 (IO26)
/MOTOR_RR: J14.5, R13.1
/MOTOR_RR_RAW: R13.2, U1.8 (IO32)
/SPI_MISO: U1.31 (IO19), U2.9 (AD0/MISO)
/SPI_MOSI: U1.30 (IO18), U2.24 (SDA/MOSI)
/SPI_SCK: U1.29 (IO5), U2.23 (SCL/SCLK)
/SW_NODE: C3.1, D1.1 (K), L1.1, U3.8 (PH)
/UART0_RX: J7.2, U1.34 (RXD0/IO3), U6.21 (TXD)
/UART0_TX: J7.1, U1.35 (TXD0/IO1), U6.20 (RXD)
/USB_CC1: J9.A5 (CC1), R15.1
/USB_CC2: J9.B5 (CC2), R16.1
/USB_CONN_DM: J9.A7 (D-), J9.B7 (D-), U5.3 (I/O2)
/USB_CONN_DP: J9.A6 (D+), J9.B6 (D+), U5.1 (I/O1)
/USB_DM: U5.4 (I/O2), U6.4 (D-)
/USB_DP: U5.6 (I/O1), U6.3 (D+)
/USB_SHIELD: C18.1, J9.SH (SHIELD), R20.1
/USB_VBUS: C14.1, C16.1, F1.1, U5.5 (VBUS), U6.7 (VREGIN), U6.8 (VBUS), U7.6 (IN2)
/USB_VBUS_RAW: F1.2, J9.A4 (VBUS), J9.A9 (VBUS), J9.B4 (VBUS), J9.B9 (VBUS)
/VBAT_RAW: C1.1, J1.1, J2.1, J14.6, R1.2, SW2.1 (A), U3.7 (VIN)
GND: C1.2, C2.2, C4.2, C5.2, C6.2, C7.2, C10.2, C11.2, C12.2, C13.2, C14.2, C15.2, C16.2, C17.2, C18.2, C19.2, D1.2 (A), D3.1 (K), D4.1 (K), J1.2, J2.2, J4.1, J5.1, J6.1, J7.6, J8.6, J9.A1 (GND), J9.A12 (GND), J9.B1 (GND), J9.B12 (GND), J14.7, R2.2, R7.2, R14.2, R15.2, R16.2, R17.2, R20.2, R24.2, R26.2, SW1.1, SW3.2, U1.1 (GND), U1.15 (GND), U1.38 (GND), U1.39 (GND), U2.11 (FSYNC), U2.18 (GND), U2.20 (RESV_GND), U3.6 (GND), U3.9 (GNDPAD), U4.2 (GND), U5.2 (GND), U6.2 (GND), U6.25 (GND), U7.2 (EN), U7.5 (GND)
unnamed: D3.2 (A), R22.1
unnamed: D4.2 (A), R23.1
unnamed: Q1.1 (B), R18.1
unnamed: Q2.1 (B), R19.1
unnamed: R1.1, R2.1, R3.2
unnamed: C12.1, U2.10 (REGOUT)
unnamed: C3.2, U3.1 (BOOT)
unnamed: R6.2, R7.1, U3.4 (VSENSE)
unnamed: R17.1, U7.4 (ILIM)

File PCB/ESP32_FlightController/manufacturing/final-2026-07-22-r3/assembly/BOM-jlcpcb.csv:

"Comment","Designator","Footprint","LCSC Part #"
"10uF/25V X7R","C1","C_1210_3225Metric",""
"100n","C2","C_0805_2012Metric",""
"10n","C3","C_0603_1608Metric",""
"220uF/10V LOW-ESR","C4","CP_Elec_6.3x5.8",""
"10u","C5,C6","C_0805_2012Metric",""
"1u","C7","C_0603_1608Metric",""
"10n X7R","C10","C_0402_1005Metric",""
"100n X7R","C11,C12,C13","C_0402_1005Metric",""
"4.7u X7R","C14","C_0603_1608Metric",""
"100n","C15,C16,C19","C_0603_1608Metric",""
"10u X7R","C17","C_0805_2012Metric",""
"1nF/2kV","C18","C_1206_3216Metric",""
"B340A","D1","D_SMA",""
"GREEN_POWER","D3","LED_0603_1608Metric",""
"BLUE_STATUS","D4","LED_0603_1608Metric",""
"0.75A USB PTC","F1","Fuse_1206_3216Metric",""
"XT60_FC_FEED_PIGTAIL","J1","SolderWire-1.5sqmm_1x02_P6mm_D1.7mm_OD3mm",""
"3S_BAT_SENSE","J2","JST_GH_BM02B-GHS-TBT_1x02-1MP_P1.25mm_Vertical",""
"I2C_SENSOR_BUS","J4","JST_SH_BM04B-SRSS-TB_1x04-1MP_P1.00mm_Vertical",""
"GPS_NEO6M","J5","JST_GH_BM04B-GHS-TBT_1x04-1MP_P1.25mm_Vertical",""
"FLYSKY_IBUS","J6","JST_GH_BM03B-GHS-TBT_1x03-1MP_P1.25mm_Vertical",""
"UART_PROGRAM","J7","PinHeader_1x06_P1.27mm_Vertical",""
"JTAG_DEBUG","J8","PinHeader_1x06_P1.27mm_Vertical",""
"USB_C_PROGRAM","J9","USB_C_Receptacle_GCT_USB4105-xx-A_16P_TopMnt_Horizontal",""
"BLS60A_ESC_7PIN","J14","JST_SH_BM07B-SRSS-TB_1x07-1MP_P1.00mm_Vertical",""
"15uH SRP7028A-150M","L1","L_Bourns_SRP7028A_7.3x6.6mm",""
"MMBT3904","Q1,Q2","SOT-23",""
"235k 1%","R1","R_0805_2012Metric",""
"35k 1%","R2","R_0805_2012Metric",""
"1k","R3","R_0805_2012Metric",""
"4.7k","R4,R5","R_0805_2012Metric",""
"10k 1%","R6,R21,R25","R_0603_1608Metric",""
"3.24k 1%","R7","R_0603_1608Metric",""
"10k","R8,R9,R18,R19","R_0603_1608Metric",""
"220","R10,R11,R12,R13","R_0805_2012Metric",""
"100k","R14","R_0603_1608Metric",""
"5.1k","R15,R16","R_0603_1608Metric",""
"499R (1A LIMIT)","R17","R_0603_1608Metric",""
"1M","R20","R_0603_1608Metric",""
"2.2k","R22,R23","R_0603_1608Metric",""
"20k 1%","R24,R26","R_0603_1608Metric",""
"RESET","SW1","SW_SPST_CK_KXT3",""
"CONTROLLER_POWER","SW2","SW_SPST_CK_RS282G05A3",""
"BOOT","SW3","SW_SPST_CK_KXT3",""
"ESP32-WROOM-32E","U1","ESP32-WROOM-32_Custom",""
"MPU-9250","U2","InvenSense_QFN-24_3x3mm_P0.4mm",""
"TPS5430DDA","U3","TI_SO-PowerPAD-8_NoUnderDrills",""
"AP2112K-3.3","U4","SOT-23-5",""
"USBLC6-2SC6","U5","SOT-23-6",""
"CP2102N-A02-GQFN24","U6","QFN-24-1EP_4x4mm_P0.5mm_EP2.7x2.7mm",""
"TPS2113APW","U7","TSSOP-8_3x3mm_P0.65mm",""

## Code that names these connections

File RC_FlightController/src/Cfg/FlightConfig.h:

#pragma once

// FlightConfig.h is the first file to open when adapting the aircraft.
// It contains hardware assignments, safe flight defaults, filter settings,
// and task timing. Runtime values changed by the GCS are stored separately in
// ESP32 NVS and override the TUNE_* defaults after boot.

#include <cstddef>
#include <cstdint>

// Hardware pins -------------------------------------------------------------
constexpr uint8_t PIN_SPI_SCK = 5;
constexpr uint8_t PIN_SPI_MISO = 19;
constexpr uint8_t PIN_SPI_MOSI = 18;
constexpr uint8_t PIN_MPU_CS = 33;
constexpr uint8_t PIN_MPU_INT = 27;
constexpr uint8_t PIN_MOTOR_FL = 25;
constexpr uint8_t PIN_MOTOR_FR = 4;
constexpr uint8_t PIN_MOTOR_RL = 26;
constexpr uint8_t PIN_MOTOR_RR = 32;
constexpr uint8_t PIN_IBUS_RX = 16;
constexpr uint8_t PIN_IBUS_TX = 2;
constexpr uint8_t PIN_BMP_SDA = 21;
constexpr uint8_t PIN_BMP_SCL = 22;
constexpr uint8_t PIN_GPS_RX = 23;
constexpr uint8_t PIN_GPS_TX = 17;
constexpr uint8_t PIN_BATTERY_ADC = 34;

// Control-loop timing and filtering -----------------------------------------
constexpr size_t TIMING_BUF_SIZE = 800;
constexpr uint32_t TIMING_TARGET_US = 2500;
constexpr uint32_t JITTER_VIOLATION_US = 100;
constexpr float GYRO_LPF_HZ = 50.0f;
constexpr float RC_LPF_HZ = 70.0f;

// Time-of-flight sensor ------------------------------------------------------
constexpr uint8_t TOF_ST_ADDRESS = 0x12;
constexpr uint32_t TOF_I2C_HZ = 400000;
constexpr uint32_t TOF_TIMING_BUDGET_US = 20000;
constexpr uint32_t TOF_INTER_MEASUREMENT_MS = 25;
constexpr uint32_t TOF_TASK_PERIOD_MS = 25;
constexpr uint32_t TOF_STALE_MS = 200;

// ToF altitude hold ----------------------------------------------------------
constexpr float TUNE_ALT_HOLD_KP = 0.080f;      // throttle trim per metre error
constexpr float TUNE_ALT_HOLD_KD = 0.040f;      // throttle trim per m/s vertical speed
constexpr float TUNE_ALT_HOLD_MAX_TRIM = 0.120f;
constexpr float TUNE_ALT_HOLD_MIN_TOF_M = 0.05f;
constexpr float TUNE_ALT_HOLD_MAX_TOF_M = 3.50f;

// Pilot limits and motor authority ------------------------------------------
constexpr float TUNE_MAX_ANGLE_DEG = 5.0f;
constexpr float TUNE_MAX_RATE_DPS = 200.0f;
constexpr float TUNE_ROLL_OUTPUT_LIMIT = 0.120f;
constexpr float TUNE_PITCH_OUTPUT_LIMIT = 0.120f;
constexpr float TUNE_YAW_OUTPUT_LIMIT = 0.120f;

// Throttle shaping ----------------------------------------------------------
constexpr float TUNE_THROTTLE_EXPO = 0.70f;
constexpr float TUNE_THROTTLE_UP_RATE_PER_SEC = 0.50f;
constexpr float TUNE_THROTTLE_DOWN_RATE_PER_SEC = 0.50f;
constexpr float TUNE_MOTOR_IDLE = 0.08f;
constexpr float TUNE_MOTOR_MAX = 1.00f;
constexpr float TUNE_THROTTLE_CUT = 0.03f;
constexpr float TUNE_IDLE_RAMP_END = 0.15f;

// Rate-loop PID defaults -----------------------------------------------------
constexpr float TUNE_RATE_ROLL_KP = 0.001300f;
constexpr float TUNE_RATE_ROLL_KI = 0.000700f;
constexpr float TUNE_RATE_ROLL_KD = 0.000000010f;
constexpr float TUNE_RATE_ROLL_FF = 0.000000f;
constexpr float TUNE_RATE_ROLL_D_LPF_HZ = 100.0f;
constexpr float TUNE_RATE_PITCH_KP = 0.001300f;
constexpr float TUNE_RATE_PITCH_KI = 0.000700f;
constexpr float TUNE_RATE_PITCH_KD = 0.000000010f;
constexpr float TUNE_RATE_PITCH_FF = 0.000000f;
constexpr float TUNE_RATE_PITCH_D_LPF_HZ = 100.0f;
constexpr float TUNE_RATE_YAW_KP = 0.008000f;
constexpr float TUNE_RATE_YAW_KI = 0.001000f;
constexpr float TUNE_RATE_YAW_KD = 0.0000000f;
constexpr float TUNE_RATE_YAW_FF = 0.000000f;
constexpr float TUNE_RATE_YAW_D_LPF_HZ = 100.0f;

// Angle-loop and yaw-hold PID defaults --------------------------------------
constexpr float TUNE_ANGLE_ROLL_KP = 1.50f;
constexpr float TUNE_ANGLE_ROLL_KI = 0.000f;
constexpr float TUNE_ANGLE_ROLL_KD = 0.000000f;
constexpr float TUNE_ANGLE_PITCH_KP = 1.00f;
constexpr float TUNE_ANGLE_PITCH_KI = 0.000f;
constexpr float TUNE_ANGLE_PITCH_KD = 0.000000f;
constexpr float TUNE_ANGLE_YAW_KP = 1.00f;
constexpr float TUNE_YAW_DEADBAND = 0.02f;
constexpr float TUNE_YAW_MAX_RATE_DPS = 20.0f;

// Vibration filtering -------------------------------------------------------
constexpr bool TUNE_NOTCH_ENABLE = true;
constexpr float TUNE_NOTCH_FREQ_HZ = 105.38f;
constexpr float TUNE_NOTCH_Q = 10.0f;
constexpr float NOTCH_SAMPLE_HZ = 400.0f;
constexpr bool TUNE_DYNAMIC_NOTCH_ENABLE = true;
constexpr float DYN_NOTCH_MIN_HZ = 45.0f;
constexpr float DYN_NOTCH_MAX_HZ = 170.0f;
constexpr uint32_t DYN_NOTCH_UPDATE_MS = 1000;
constexpr float DYN_NOTCH_ALPHA = 0.25f;
constexpr float DYN_NOTCH_MAX_STEP_HZ = 8.0f;
constexpr float DYN_NOTCH_MIN_THROTTLE = 0.15f;
constexpr float DYN_NOTCH_MIN_SCORE = 3.5f;

// Runtime diagnostics -------------------------------------------------------
constexpr bool LOG_CONTROL_TIMING = true;
constexpr bool LOG_MOTOR_SATURATION = false;
constexpr bool LOG_MOTOR_WRITE_RATE = false;
constexpr bool LOG_DYNAMIC_NOTCH_DEBUG = false;

// Attitude-estimator defaults -----------------------------------------------
constexpr float TUNE_EKF_ANGLE_Q = 0.0008f;
constexpr float TUNE_EKF_BIAS_Q = 0.000001f;
constexpr float TUNE_EKF_ACCEL_R = 0.400f;
constexpr float TUNE_EKF_MAG_R = 0.200f;
constexpr float TUNE_EKF_MAG_DECL_DEG = 0.0f;
constexpr float TUNE_EKF_MAG_YAW_OFF_DEG = 0.0f;
constexpr float TUNE_EKF_MAG_YAW_SIGN = 1.0f;
constexpr float TUNE_AHRS_FILTER_MODE = 0.0f;
constexpr float TUNE_MADGWICK_BETA = 0.080f;

// Calibration and level-zero capture ---------------------------------------
constexpr uint32_t LEVEL_ZERO_SAMPLE_MS = 1200;
constexpr uint16_t LEVEL_ZERO_SWB_THRESHOLD = 1700;
constexpr uint16_t SWC_THRESHOLD = 1700;
constexpr uint16_t ESC_CALIB_VRB_THRESHOLD = 1900;
constexpr uint32_t GYRO_SETTLE_MS = 3000;
constexpr uint32_t GYRO_SAMPLE_MS = 5000;
constexpr uint32_t ACCEL_HOLD_MS = 3000;
constexpr uint32_t ACCEL_WAIT_MAX_MS = 30000;
constexpr uint32_t MAG_DURATION_MS = 30000;

// Aircraft and battery ------------------------------------------------------
constexpr float MOTOR_KV = 920.0f;
constexpr float BATTERY_NOMINAL_V = 11.1f;
constexpr uint8_t BATTERY_CELL_COUNT = 3;
constexpr float BATTERY_RTOP_OHMS = 235000.0f;
constexpr float BATTERY_RBOTTOM_OHMS = 35000.0f;
constexpr float BATTERY_ADC_CAL_SCALE = 1.0f;
constexpr uint16_t FLIGHT_LOGGER_CAPACITY = 120;

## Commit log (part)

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2026-05-15 5/15/2026 - Initial Commit with MPU freetos implementation
2026-05-15 05/12/2026 - clean up commit
2026-05-15 5/15/2026 - Commit for Simulation interface (webBased) and code update
2026-05-16 Improve Wi-Fi telemetry with client discovery and safer packet formatting
2026-05-16 05/15/2026 - Commit for telemetry libs
2026-05-16 05/15/2026 - Commit for BMP Lib
2026-05-16 05/15/2026 - Commit for BMP sensor Lib
2026-05-16 05/16/2026 - Commit for CPU utilization
2026-05-16 05/16/2026 - Commit for improved groundstation and flight controller
2026-05-16 05/16/2026 - Commit for PCB
2026-05-18 05/18/2026 - Commit for Motor controls
2026-05-18 05/18/2026 - Commit for fixing the WiFi Telemetry stack t0 12288
2026-05-18 05/18/2026 - Commit for including Motor Control Lib
2026-05-19 05/18/2026 - Commit for GPS addition
2026-05-19 05/18/2026 - Readme Update
2026-05-21 05/20/2026 - Commit for first Flight Test Code
2026-05-27 05/27/2026 - Commit for test
2026-05-28 Jitter Reduction code
2026-05-28 Fix for RC hz reading frame rates
2026-06-02 First Flight Code
2026-06-03 PID Tuning reduced gain cahnged calibration conventions
2026-06-04 PID Tuning and Throttle Smoothening added + motor Idle Floor added
2026-06-04 Adding LPF for throttle and Gyro and improved oscillations
2026-06-04 Some Code improvements making it easy to find values at one single place
2026-06-05 Some Code improvements
2026-06-07 First Stable ACRO flight - gain scheduling good for inner loop
2026-06-07 First Stable ACRO flight - Groundstation Precision Update
2026-06-08 Enabling OTA feature and adding precompiled bin Files + Adding Updated GSC to handle all the tuning parameters.
2026-06-08 Adding offline MAP
2026-06-08 docs: add offline OSM map workflow
2026-06-08 adding OTA update to GSC
2026-06-08 BMP Tele Bug Fix
2026-06-10 Update RC_FlightController.ino
    PID tuning updates after crash
2026-06-10 Bin File to be commited.
    Binary file For PID Tuning after the Crash
2026-06-12 Add loop execution timing measurement patch
2026-06-13 Fixes for Jitter issue sof control task
2026-06-13 Fixies Jitter Issue
2026-06-14 Fixies Jitter Issue Telemettry issue and tunning Issue fix
2026-06-14 Application for Android + AHRS + Offset Logic
2026-06-15 Fix Github repo issues
    A lot of files for Android app was uploaded this commit removes those files
2026-06-18 New Feature Pack
2026-06-18 Spectrum Analyser added for motor Vibration
2026-06-23 Added Architecture splits
2026-06-23 Added Dynamic Notch Filter
2026-06-24 Added Dynamic Notch Filter 2nd flight
2026-06-24 Fix flight timing stability build issues
2026-06-24 Update README documentation
2026-06-24 Gate Serial prints behind VERNOSE_ON
2026-06-24 Rename verbose build flag
2026-06-24 Add detailed module READMEs
2026-06-24 Convert libraries to git submodules
2026-06-24 Update module README submodule refs
2026-06-24 Remove test-quad prefix from submodule URLs
2026-06-24 Restructure sketch for Arduino auto compile
2026-06-24 Move filters into Arduino src and add build binaries
2026-06-24 Add build folder notes
2026-06-24 Show RAM utilization percentage in build notes
2026-06-24 Remove top-level Arduino build cache
2026-06-24 Add standard headers and refresh build artifacts
2026-06-25 Set ACRO tuning defaults
2026-06-25 Update firmware binary and build metrics
2026-06-25 Apply V5 tuning defaults
2026-06-25 Add diagnostic telemetry logging mechanism
2026-06-25 Implement diagnostic telemetry logging mechanism
2026-06-25 Add GCS diagnostic logging page
2026-06-25 Document diagnostic logging integration plan
2026-06-25 Add Logger diagnostic library
2026-06-25 Implement Logger diagnostic library
2026-06-25 Add Logger diagnostics GCS page
2026-06-25 Document RC_FlightController logger integration
2026-06-25 Integrate flight logger patch
2026-06-25 Make flight logger allocation boot-safe
2026-06-25 Add WiFi logging parameter export
2026-06-25 Optimize WiFi logging telemetry path
2026-06-26 Fix WiFi CSV telemetry zeros
2026-06-26 Update EKF accel weighting
2026-06-26 Update flight tuning calibration defaults
2026-06-26 Update EKF passive navigation estimate
2026-06-26 Align GCS calibration defaults
2026-06-26 Populate WiFi log timing metrics
2026-06-26 Add magnetometer health log fields
2026-06-26 Show calibration manager in system log
2026-06-26 Set default motor max to full output
2026-06-26 Add firmware identity reporting
2026-06-26 Build firmware with identity signature
2026-06-26 Allow full motor output and scroll GCS tabs
2026-06-26 Build firmware with full motor output
2026-06-26 Add config tab scrollbars
2026-06-26 Tune dynamic notch tracking response
2026-06-26 Build firmware with dynamic notch tune
2026-06-26 Fix config section scroll containers
2026-06-26 Reduce GCS WiFi polling load
2026-06-28 Add QuadStack promotion metadata
2026-06-28 Tune dynamic notch and rename FlightStack
2026-06-28 Add debug and release firmware binaries
2026-06-28 Revert dynamic notch response tuning
2026-06-28 Rebuild firmware after notch revert
2026-06-28 Throttle spectrum polling while armed
2026-06-30 Wire VL53L4CX ToF driver
2026-06-30 Read ToF sensor on core 0
2026-06-30 Print ToF object count in status
2026-06-30 Update firmware binaries for ToF reboot fix
